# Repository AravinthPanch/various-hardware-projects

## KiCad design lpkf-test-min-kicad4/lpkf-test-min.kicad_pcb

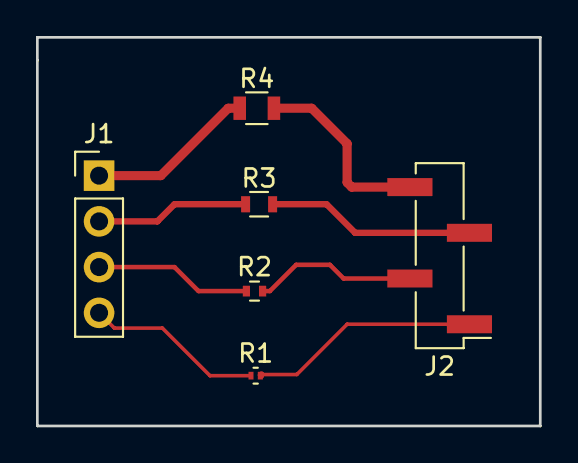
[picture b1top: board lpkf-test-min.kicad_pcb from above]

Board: 2 copper layers, 27.9 x 21.6 mm, 6 parts (0 on the bottom side), 8 nets.

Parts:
J1: LEFT; Pin_Header_Straight_1x04_Pitch2.54mm
J2: RIGHT; Pin_Header_Straight_1x04_Pitch2.54mm_SMD_Pin1Left
R1: 1K; R_0201
R2: 1K; R_0402
R3: 1K; R_0603
R4: 1K; R_0805

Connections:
unnamed: J1.1, R4.1
unnamed: J1.2, R3.1
unnamed: J1.3, R2.1
unnamed: J1.4, R1.1
unnamed: J2.1, R1.2
unnamed: J2.2, R2.2
unnamed: J2.3, R3.2
unnamed: J2.4, R4.2

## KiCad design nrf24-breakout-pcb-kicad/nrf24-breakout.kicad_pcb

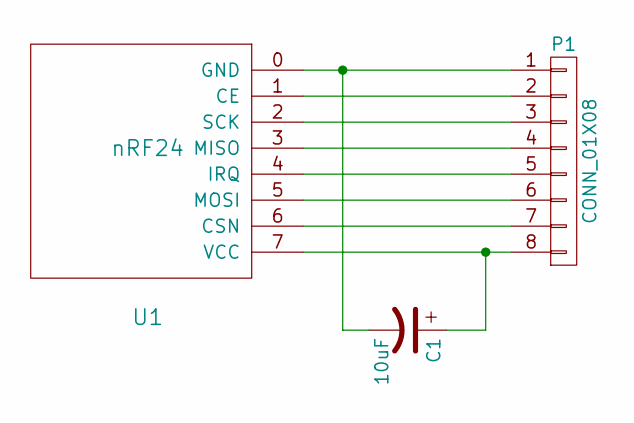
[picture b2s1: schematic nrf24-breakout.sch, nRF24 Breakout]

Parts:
C1: 10uF; CP_Radial_D10.0mm_P5.00mm
P1: CONN_01X08; Pin_Header_Straight_1x08
U1: nRF24; nrf24

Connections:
unnamed: C1.1, P1.8, U1.7 (VCC)
unnamed: C1.2, P1.1, U1.0 (GND)
unnamed: P1.2, U1.1 (CE)
unnamed: P1.3, U1.2 (SCK)
unnamed: P1.4, U1.3 (MISO)
unnamed: P1.5, U1.4 (IRQ)
unnamed: P1.6, U1.5 (MOSI)
unnamed: P1.7, U1.6 (CSN)

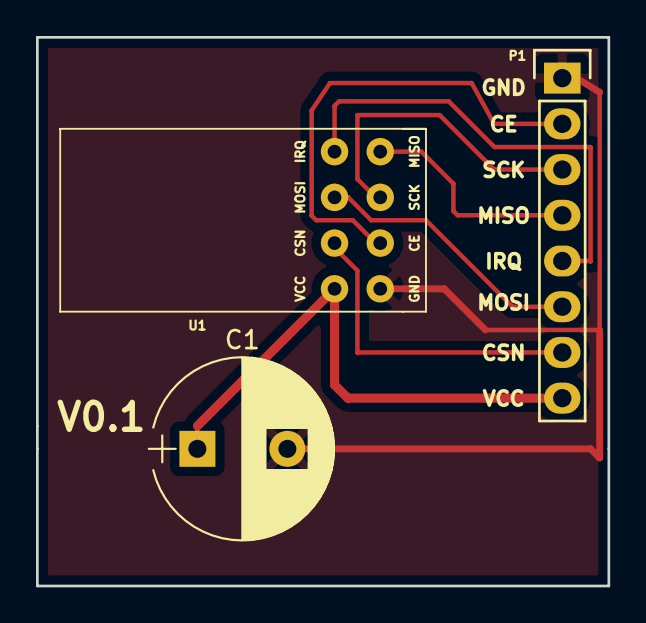
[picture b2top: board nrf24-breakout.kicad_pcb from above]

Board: 2 copper layers, 31.8 x 30.5 mm, 3 parts (0 on the bottom side), 8 nets.
